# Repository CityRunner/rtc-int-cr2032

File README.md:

# ODIN RTC Replacement

Drop-in CR2032 replacement for the ODIN OEC12C887 RTC module.

- BQ3285S SSOP-24
- Replaceable CR2032
- DIP-24 socket
- Intel bus mode
- 32.768 kHz crystal

Based on [Necroware/nwX287](https://github.com/necroware/nwX287) and [ScrapComputing/nwX287.cr2032.ssop.mot](https://github.com/scrapcomputing/nwX287.cr2032.ssop.mot).

# BOM

| Ref. | Description |
| --- | --- |
| BT1 | CR2032 holder |
| U1 | BQ3285S SSOP-24 |
| U2 | DIP-24 socket |
| Y1 | 32.768 kHz crystal |

Use a non-rechargeable CR2032.

See the KiCad files for the schematic and PCB.

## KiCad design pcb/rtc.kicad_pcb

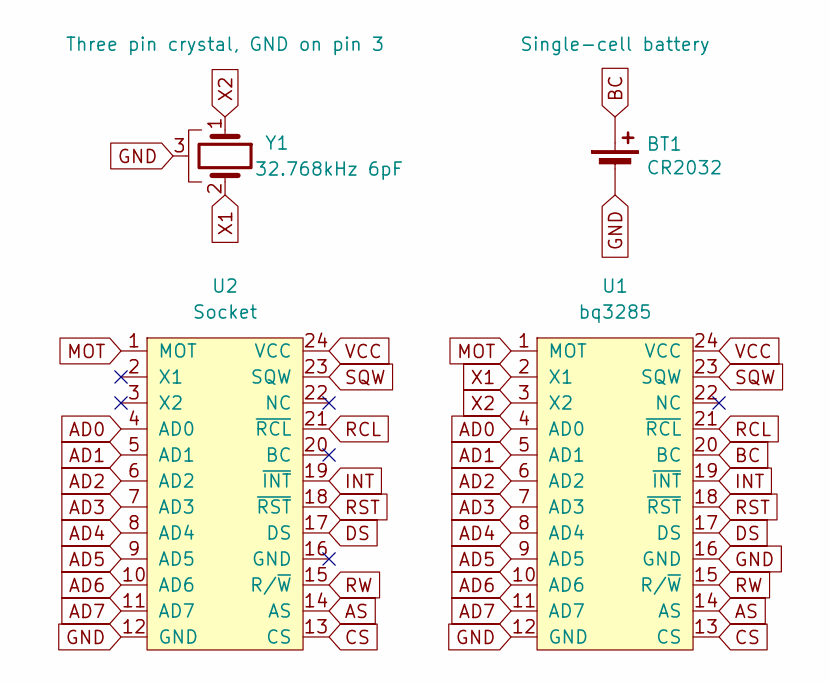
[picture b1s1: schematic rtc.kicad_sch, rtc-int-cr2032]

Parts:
BT1: CR2032; BatteryHolder_MYOUNG_BS-07-A1BJ001_CR2032
U1: bq3285; SSOP-24_3.9x8.7mm_P0.635mm
U2: Socket; DIP-24_W15.24mm_Socket
Y1: 32.768kHz 6pF; Crystal_SMD_FrontierElectronics_FM206

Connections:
AD0: U1.4 (AD0), U2.4 (AD0)
AD1: U1.5 (AD1), U2.5 (AD1)
AD2: U1.6 (AD2), U2.6 (AD2)
AD3: U1.7 (AD3), U2.7 (AD3)
AD4: U1.8 (AD4), U2.8 (AD4)
AD5: U1.9 (AD5), U2.9 (AD5)
AD6: U1.10 (AD6), U2.10 (AD6)
AD7: U1.11 (AD7), U2.11 (AD7)
AS: U1.14 (AS), U2.14 (AS)
BC: BT1.1 (+), U1.20 (BC)
CS: U1.13 (CS), U2.13 (CS)
DS: U1.17 (DS), U2.17 (DS)
GND: BT1.2 (-), U1.12 (GND), U1.16 (GND), U2.12 (GND), Y1.3
INT: U1.19 (~INT), U2.19 (~INT)
MOT: U1.1 (MOT), U2.1 (MOT)
RCL: U1.21 (~RCL), U2.21 (~RCL)
RST: U1.18 (~RST), U2.18 (~RST)
RW: U1.15 (R/~W), U2.15 (R/~W)
SQW: U1.23 (SQW), U2.23 (SQW)
VCC: U1.24 (VCC), U2.24 (VCC)
X1: U1.2 (X1), Y1.2
X2: U1.3 (X2), Y1.1

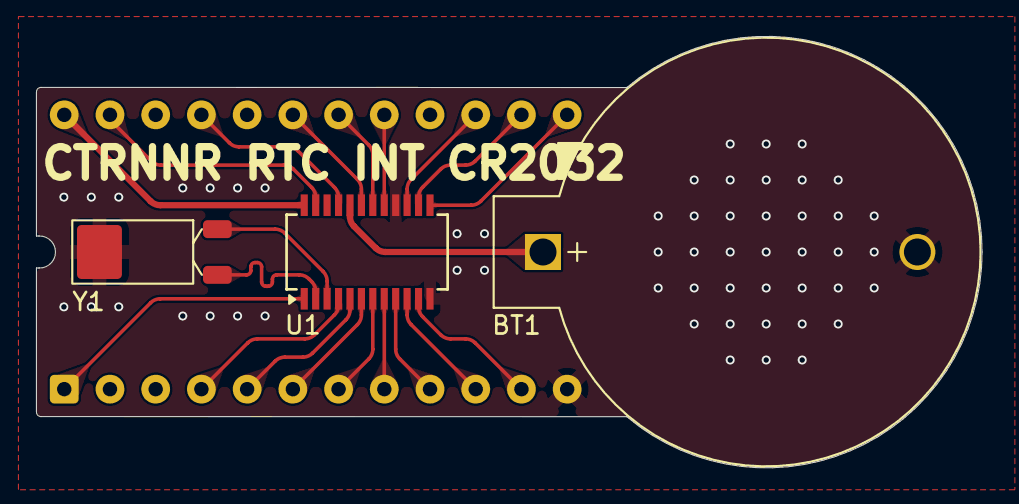
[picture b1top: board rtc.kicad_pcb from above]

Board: 2 copper layers, 52.5 x 24.0 mm, 4 parts (0 on the bottom side), 22 nets.
